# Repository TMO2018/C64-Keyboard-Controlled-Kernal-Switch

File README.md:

# C64-Keyboard-Controlled-Kernal-Switch for 6526

This project is based on the C64 Keyboard Controlled Kernal Switch Rev. 1.0 from Sven Petersen  (github: svenpetersen1965). For additional informations take a look at Sven Petersens github repository. 

The original kernal switch ist directly connected to the C64 keyboard connector. In my C64 (bread box) with board Assy 250407 the Kernal Switch lies on the fastening screw and other components with the risk of an electrical connection. So I developed an alternative.
The kernal switch 6526 is an intermediate socket for the 6526 on U1.

Advantage:
- better mechanical stability
- SMD soldering pads for hand soldering

Disadvantage:
- additional line for querying the restore button
- if the 6526 is not socketed, it must be unsoldered

Rev 1.0: Design based on Sven Petersens C64 Keyboard Controlled Kernal Switch (ATmega with external clock at 16 MHz), 8 kernals

Rev 2.0: Cost-reduced Design (ATmega with internal clock at 8 MHz), 8 kernals

Rev 3.0: Expansion from 8 to 14 kernals. Based on Rev 2.0.

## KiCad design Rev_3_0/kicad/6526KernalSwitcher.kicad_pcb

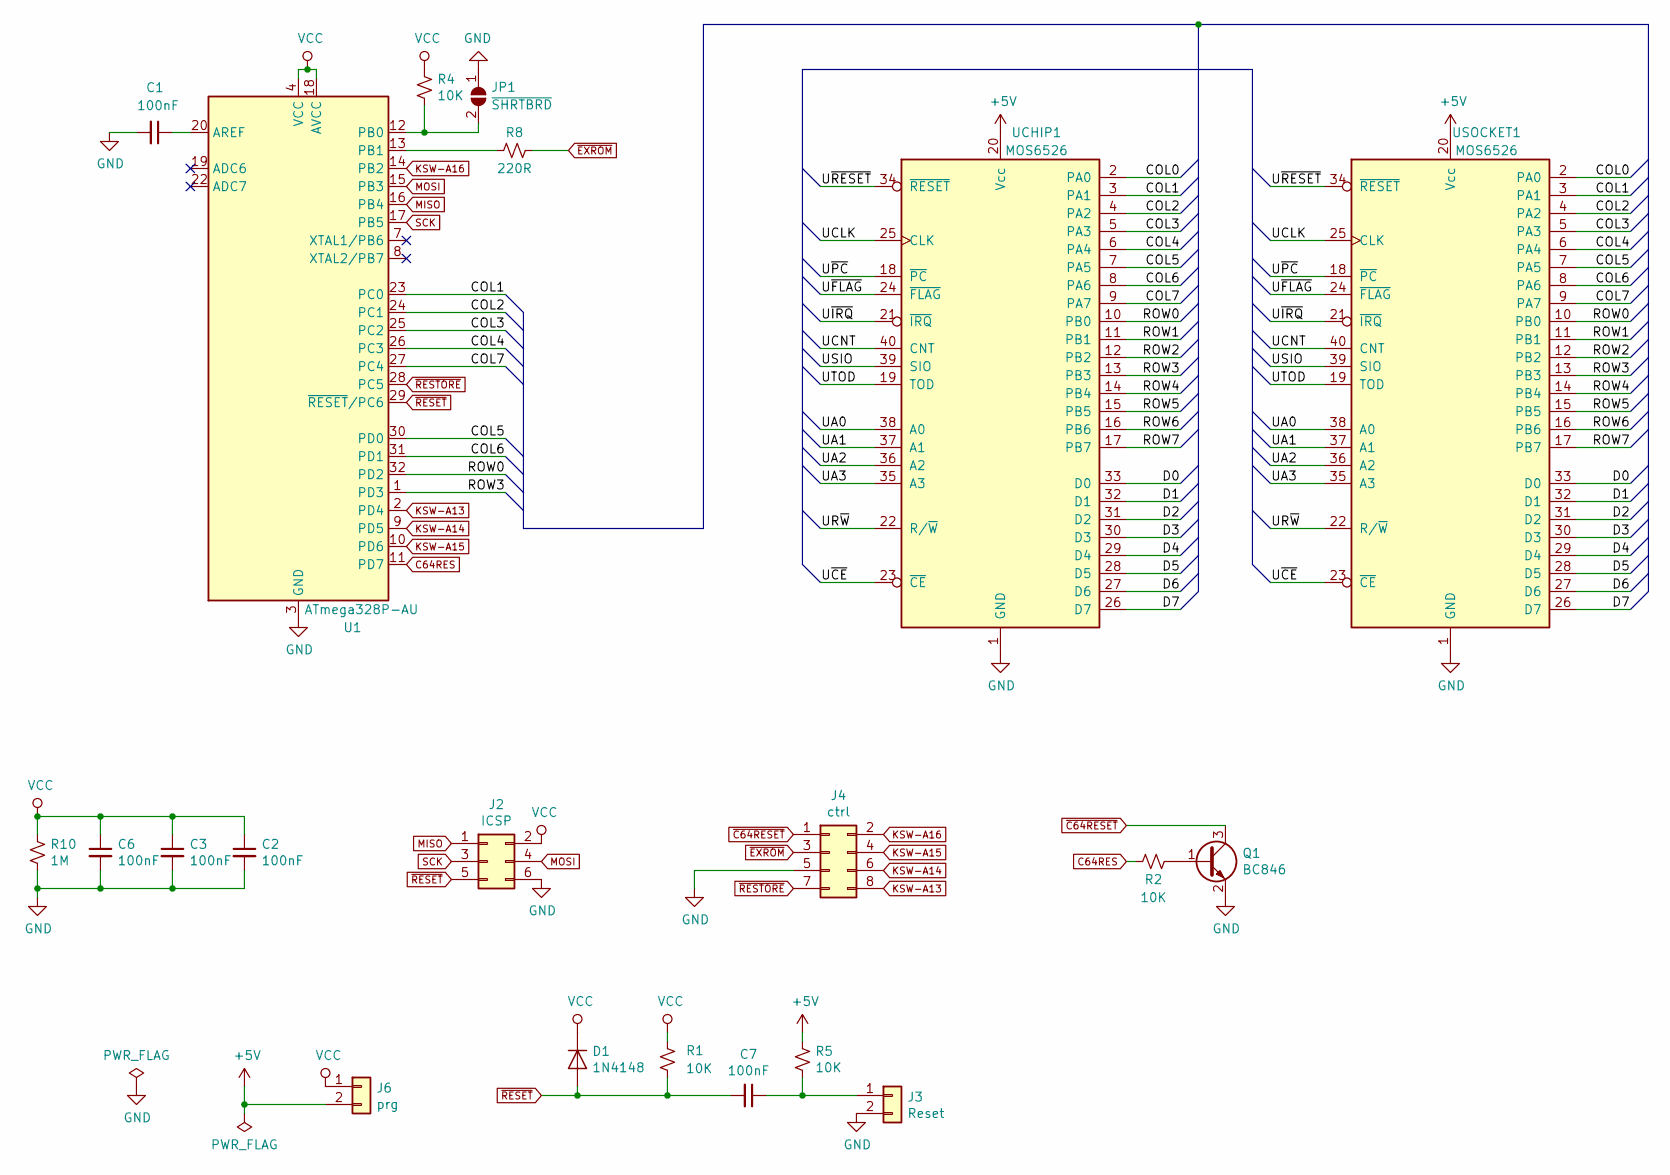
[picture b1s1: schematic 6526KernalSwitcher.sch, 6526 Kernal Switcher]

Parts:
C1, C2, C3, C6, C7: 100nF; C_0805_HandSoldering
D1: 1N4148; D_MicroMELF_Hadsoldering
J2: ICSP; Pin_Header_Straight_2x03_Pitch2.54mm
J3: Reset; Pin_Header_Angled_1x02_Pitch2.54mm_no_silk
J4: ctrl; Pin_Header_Angled_2x04_Pitch2.54mm_no_silk
J6: prg; Pin_Header_Straight_1x02_Pitch2.54mm
JP1: ~SHRTBRD; SolderJumper-2_P1.3mm_Open_RoundedPad1.0x1.5mm
Q1: BC846; SOT-23_Handsoldering
R1, R2, R4, R5: 10K; R_0805_HandSoldering
R8: 220R; R_0805_HandSoldering
R10: 1M; R_0805_HandSoldering
U1: ATmega328P-AU; TQFP-32_7x7mm_Pitch0.8mm
UCHIP1: MOS6526; DIP-40_W15.24mm
USOCKET1: MOS6526; DIP-40_W15.24mm_Pin_Rows_TMO

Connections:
+5V: J6.2, R5.1, UCHIP1.20 (Vcc), USOCKET1.20 (Vcc)
/COL0: UCHIP1.2 (PA0), USOCKET1.2 (PA0)
/COL1: U1.23 (PC0), UCHIP1.3 (PA1), USOCKET1.3 (PA1)
/COL2: U1.24 (PC1), UCHIP1.4 (PA2), USOCKET1.4 (PA2)
/COL3: U1.25 (PC2), UCHIP1.5 (PA3), USOCKET1.5 (PA3)
/COL4: U1.26 (PC3), UCHIP1.6 (PA4), USOCKET1.6 (PA4)
/COL5: U1.30 (PD0), UCHIP1.7 (PA5), USOCKET1.7 (PA5)
/COL6: U1.31 (PD1), UCHIP1.8 (PA6), USOCKET1.8 (PA6)
/COL7: U1.27 (PC4), UCHIP1.9 (PA7), USOCKET1.9 (PA7)
/D0: UCHIP1.33 (D0), USOCKET1.33 (D0)
/D1: UCHIP1.32 (D1), USOCKET1.32 (D1)
/D2: UCHIP1.31 (D2), USOCKET1.31 (D2)
/D3: UCHIP1.30 (D3), USOCKET1.30 (D3)
/D4: UCHIP1.29 (D4), USOCKET1.29 (D4)
/D5: UCHIP1.28 (D5), USOCKET1.28 (D5)
/D6: UCHIP1.27 (D6), USOCKET1.27 (D6)
/D7: UCHIP1.26 (D7), USOCKET1.26 (D7)
/ROW0: U1.32 (PD2), UCHIP1.10 (PB0), USOCKET1.10 (PB0)
/ROW1: UCHIP1.11 (PB1), USOCKET1.11 (PB1)
/ROW2: UCHIP1.12 (PB2), USOCKET1.12 (PB2)
/ROW3: U1.1 (PD3), UCHIP1.13 (PB3), USOCKET1.13 (PB3)
/ROW4: UCHIP1.14 (PB4), USOCKET1.14 (PB4)
/ROW5: UCHIP1.15 (PB5), USOCKET1.15 (PB5)
/ROW6: UCHIP1.16 (PB6), USOCKET1.16 (PB6)
/ROW7: UCHIP1.17 (PB7), USOCKET1.17 (PB7)
/UA0: UCHIP1.38 (A0), USOCKET1.38 (A0)
/UA1: UCHIP1.37 (A1), USOCKET1.37 (A1)
/UA2: UCHIP1.36 (A2), USOCKET1.36 (A2)
/UA3: UCHIP1.35 (A3), USOCKET1.35 (A3)
/UCLK: UCHIP1.25 (CLK), USOCKET1.25 (CLK)
/UCNT: UCHIP1.40 (CNT), USOCKET1.40 (CNT)
/UR~W: UCHIP1.22 (R/~W~), USOCKET1.22 (R/~W~)
/USIO: UCHIP1.39 (SIO), USOCKET1.39 (SIO)
/UTOD: UCHIP1.19 (TOD), USOCKET1.19 (TOD)
/U~CE: UCHIP1.23 (~CE~), USOCKET1.23 (~CE~)
/U~FLAG: UCHIP1.24 (~FLAG~), USOCKET1.24 (~FLAG~)
/U~IRQ: UCHIP1.21 (~IRQ~), USOCKET1.21 (~IRQ~)
/U~PC: UCHIP1.18 (~PC~), USOCKET1.18 (~PC~)
/U~RESET: UCHIP1.34 (~RESET~), USOCKET1.34 (~RESET~)
C64RES: R2.2, U1.11 (PD7)
GND: C1.2, C2.2, C3.2, C6.2, J2.6, J3.2, J4.5, JP1.1 (A), Q1.2 (E), R10.2, U1.3 (GND), U1.5 (GND), U1.21 (GND), UCHIP1.1 (GND), USOCKET1.1 (GND)
KSW-A13: J4.8, U1.2 (PD4)
KSW-A14: J4.6, U1.9 (PD5)
KSW-A15: J4.4, U1.10 (PD6)
KSW-A16: J4.2, U1.14 (PB2)
MISO: J2.1, U1.16 (PB4)
MOSI: J2.4, U1.15 (PB3)
unnamed: C1.1, U1.20 (AREF)
unnamed: C7.1, J3.1, R5.2
unnamed: JP1.2 (B), R4.2, U1.12 (PB0)
unnamed: Q1.1 (B), R2.1
unnamed: R8.2, U1.13 (PB1)
SCK: J2.3, U1.17 (PB5)
VCC: C2.1, C3.1, C6.1, D1.1 (K), J2.2, J6.1, R1.1, R4.1, R10.1, U1.4 (VCC), U1.6 (VCC), U1.18 (AVCC)
~C64RESET: J4.1, Q1.3 (C)
~EXROM: J4.3, R8.1
~RESET: C7.2, D1.2 (A), J2.5, R1.2, U1.29 (~RESET~/PC6)
~RESTORE: J4.7, U1.28 (PC5)

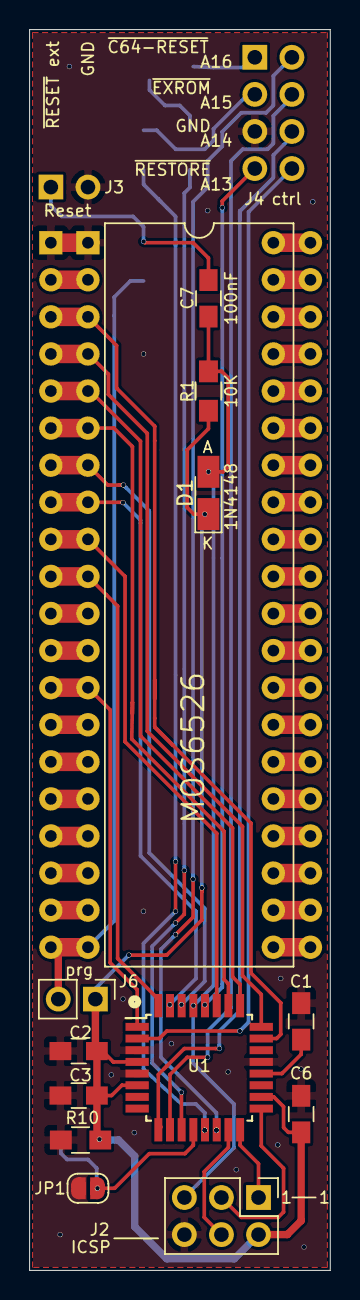
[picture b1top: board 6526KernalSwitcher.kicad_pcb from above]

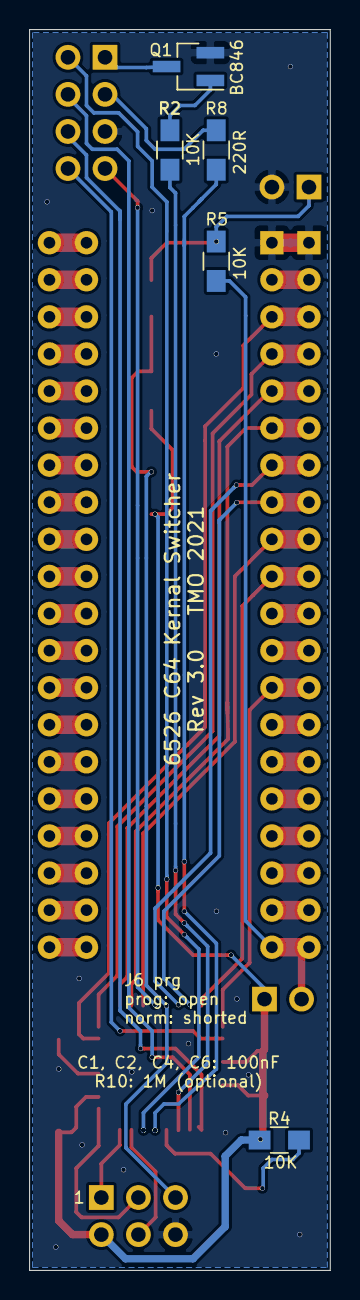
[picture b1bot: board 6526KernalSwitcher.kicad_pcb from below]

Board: 2 copper layers, 20.6 x 85.0 mm, 21 parts (5 on the bottom side), 58 nets.

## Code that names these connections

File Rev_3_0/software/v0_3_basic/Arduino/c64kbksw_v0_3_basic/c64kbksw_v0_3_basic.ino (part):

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const int  NumKernal = 14;            //This is the highest valid Kernal number
 
/* pin definitions */
const int row0 = 2;         // Row signal, input, active low, INT0
const int row3 = 3;         // Row signal, input, active low, INT1
const int KSW_A13 = 4;      // output, A13 to kernal adaptor/switch
const int KSW_A14 = 5;      // output, A14 to kernal adaptor/switch
const int KSW_A15 = 6;      // output, A15 to kernal adaptor/switch
const int C64RESET = 7;     // output, RESET signal for the C64
const int col1 = A0;        // input, column signal, active low
const int col2 = A1;        // input, column signal, active low
const int col3 = A2;        // input, column signal, active low
const int col4 = A3;        // input, column signal, active low
const int col5 = 0;        //TNO: input, column signal, active low
const int col6 = 1;        //TMO: input, column signal, active low
const int col7 = A4;        // input, column signal, active low
const int nRESTORE = A5;    // input, RESTORE key, active low
const int nSHORT_BRD = 8;   // input, short board jumper
const int nEXROM = 9;       // /EXROM Pin connected to pin header J4, pin 5 
// const int RSVD = 10;    // reserved. Pin connected to pin header J4, pin 6
//TMO: const int Signalling = 10; // Pin for signaling (LED or buzzer with tone generator), pin header J4, pin 6
const int KSW_A16 = 10; // TMO: output, A17 to kernal adaptor/switch
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#endif 

const int Restore_Count = 1500; // count appr. 2 seconds for RestoreKey before Reset
const int EXROM_Count = 3000;   // limit for EXROM reset
const int Sig_time = 500; // constant for signalling duration

/* other constants */
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byte KOffset = 0;           // offset for kernal number
byte KNumber = 0;           // Kernal number
byte KAddr = 0;             // Address bits for Kernal
bool RestoreKey = 0;        // holds the info, if the restore key is pressed 
bool oldRestoreKey = 0;     // remeber the old status to compare
int  countup = 0;           // counter for restore key time measurement
byte key = 128;             // calculate the Key
int  KMax;                  // holds the highest Kernal Number


/* Data Exchange variables for ISR (have to be volatile) */
volatile bool NumPressed = 0;  // ISR flag for number pressed
volatile bool NumOdd = 0;      // ISR flag for odd numbers. Row0 => odd numbers, Row3 => even numbers
//TMO volatile byte ColData = 0x1F;  // column data, read from PORTC
volatile byte ColData = 0x7F;  // column data, read from PORTC and PORTD

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int scan_cnt;           // 5000 miliseconds without scan changing to kernal #1 and resetting
int scan_found;         // flag for keybioard activity detected
byte inactive = 0;      // keyboard scan inactive: 1 -> inactive, 0 = active
bool exrom_mode = 0;    // exrom reset: 0 => no, 1 => yes
int signalling_cnt = 0; // count down for signalling pin

void setup() {
  /* keyboard scan signals */
  pinMode( row0, INPUT_PULLUP);  // pullup required for MOS logic
  pinMode( row3, INPUT_PULLUP);  // pullup required for MOS logic
  pinMode( col1, INPUT_PULLUP);  // pullup required for MOS logic
  pinMode( col2, INPUT_PULLUP);  // pullup required for MOS logic
  pinMode( col3, INPUT_PULLUP);  // pullup required for MOS logic
  pinMode( col4, INPUT_PULLUP);  // pullup required for MOS logic
  pinMode( col5, INPUT_PULLUP);  //TMO: pullup required for MOS logic
  pinMode( col6, INPUT_PULLUP);  //TMO: pullup required for MOS logic
  pinMode( col7, INPUT_PULLUP);  // pullup required for MOS logic
  pinMode( nRESTORE, INPUT_PULLUP);  // pullup required for MOS logic
  pinMode( nEXROM, INPUT );      // it needs to be high impedance, will switch to LOW and OUTPUT when required.
  digitalWrite( nEXROM, HIGH );
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    inactive = 0;
    EEPROM.write(EEPROMAddr+1, inactive);
  }
  exrom_mode = 0;                               // initialize exrom mode (for reset). 0 = no exrom reset
  
  KAddr = KNumber - 1 + KOffset; // Calculate the address bits.
  // For long boards, it should be between 0 and 7,
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  pinMode( KSW_A15, OUTPUT );     // make it an output
  pinMode( KSW_A16, OUTPUT );     // TMO: make it an output   
  digitalWrite( C64RESET, LOW );  // no reset for the C64
  pinMode( C64RESET, OUTPUT );    // make it an output

  if (recover_empty == true) {
    scan_cnt = ScanDelay;         // reset scan countdown
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    scan_found = true;
    scan_cnt = 0;
  }  
  attachInterrupt(digitalPinToInterrupt(row0), ISR_row0, LOW); 
  attachInterrupt(digitalPinToInterrupt(row3), ISR_row3, LOW);

/*TMO:  Serial.begin(9600);  // start serial interface
  /* output status etc. */
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
/* This function sets the address bits on the pin header J4. Parameter is addr (0..7) */
void SetAddressBits( byte addr ) {
   digitalWrite( C64RESET, HIGH );                              // do it, while /reset is low (samle like the port pin is high)
   delay (50 );                                                 // wait 50 ms
   if ((addr & 1) == 0) {         // A13                  
    digitalWrite(KSW_A13, LOW);
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  digitalWrite( C64RESET, HIGH );                            // issue a reset pulse for the C64
  delay( 100 );                                              // 100ms delay
  if (exrom_mode == 1) {
    digitalWrite( nEXROM, LOW );                             // exrom pin low
    pinMode( nEXROM, OUTPUT );                               // and output
  }
  delay( 300 );                                              // pulse duration: 100+300ms
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  if (exrom_mode == 1) {
    delay( 300 );                                            // EXROM should be 300ms longer LOW than RESET
    pinMode( nEXROM, INPUT );                                // and input = high impedance (HIZ)
    digitalWrite( nEXROM, HIGH );                            // exrom pin high
  }
  if ((recover_empty == true) && (inactive == 0)) {
    scan_cnt = ScanDelay;                                    // reset scan countdown
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//TMO:    ColData = PINC & 0x1F;               // read the columns
     ColData = (PINC & 0x1F) | ((PIND & 0x03) << 5);       //TMO: read the columns, PIND bitshift um 5 nach links
     scan_found = true;                   // any activity here indicates a working kernal
     NumOdd = 1;                          // row0 has the odd numbers
//TMO:     if ((ColData != 0x1F) && (ColData !=0)) {               // only set the flag, when a number is pressed 
     if ((ColData != 0x7F) && (ColData !=0)) {               //TMO: only set the flag, when a number is pressed
       NumPressed = 1;
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//TMO:    ColData = PINC & 0x1F;               // read the columns
     ColData = (PINC & 0x1F) | ((PIND & 0x03) << 5);        //TMO: read the columns, PIND bitshift um 5 nach links
     scan_found = true;                   // any activity here indicates a working kernal
     NumOdd = 0;                          // row3 has the even numbers
//TMO:      if ((ColData != 0x1F) && (ColData !=0)) { // only set the flag, when a number is pressed 
     if ((ColData != 0x7F) && (ColData !=0)) {               //TMO: only set the flag, when a number is pressed
       NumPressed = 1;
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          exrom_mode = 0;
        }
     }
     RestoreKey = 0;                      // in case the reading is HIGH, the Restore key is not pressed
     countup = 0;                         // restart the count down
  }
  else {
    RestoreKey = 1;                       // in case the restore is pressed, count up
    countup++;
    if (countup == Restore_Count ) {
//TMO:        digitalWrite( Signalling, !sig_idle );
       signalling_cnt = Sig_time;
    }
    if (countup > EXROM_Count) {          // time limit for EXROM reached?
       exrom_mode = 1;                    // activate EXROM mode
//TMO:       Serial.println("EXROM mode: Restore key => Reseting the C64");
       ResetC64();                        // reset the C64
       RestoreKey = 0;                    // restart the restore key
       countup = 0;                       // restart the count down
       exrom_mode = 0;                    // reset EXROM mode
    }
  }
  if (signalling_cnt > 0) {
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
